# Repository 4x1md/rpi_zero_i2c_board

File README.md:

# I2C Peripherals Board for Raspberry Pi Zero

The board was developed for communicating some I2C peripherals connected to a Raspberry Pi Zero.

## Schematics

## 3D Model

## Questions? Suggestions?

You are more than welcome to contact me with any questions, suggestions or propositions regarding this project. Please drop an email to ```iosaaris =at= gmail dot com```.

## How to Support or Say Thanks

If you like this project, or found here some useful information and want to say thanks, or encourage me to do more, you can buy me a coffee!

---

73 de 4X1MD

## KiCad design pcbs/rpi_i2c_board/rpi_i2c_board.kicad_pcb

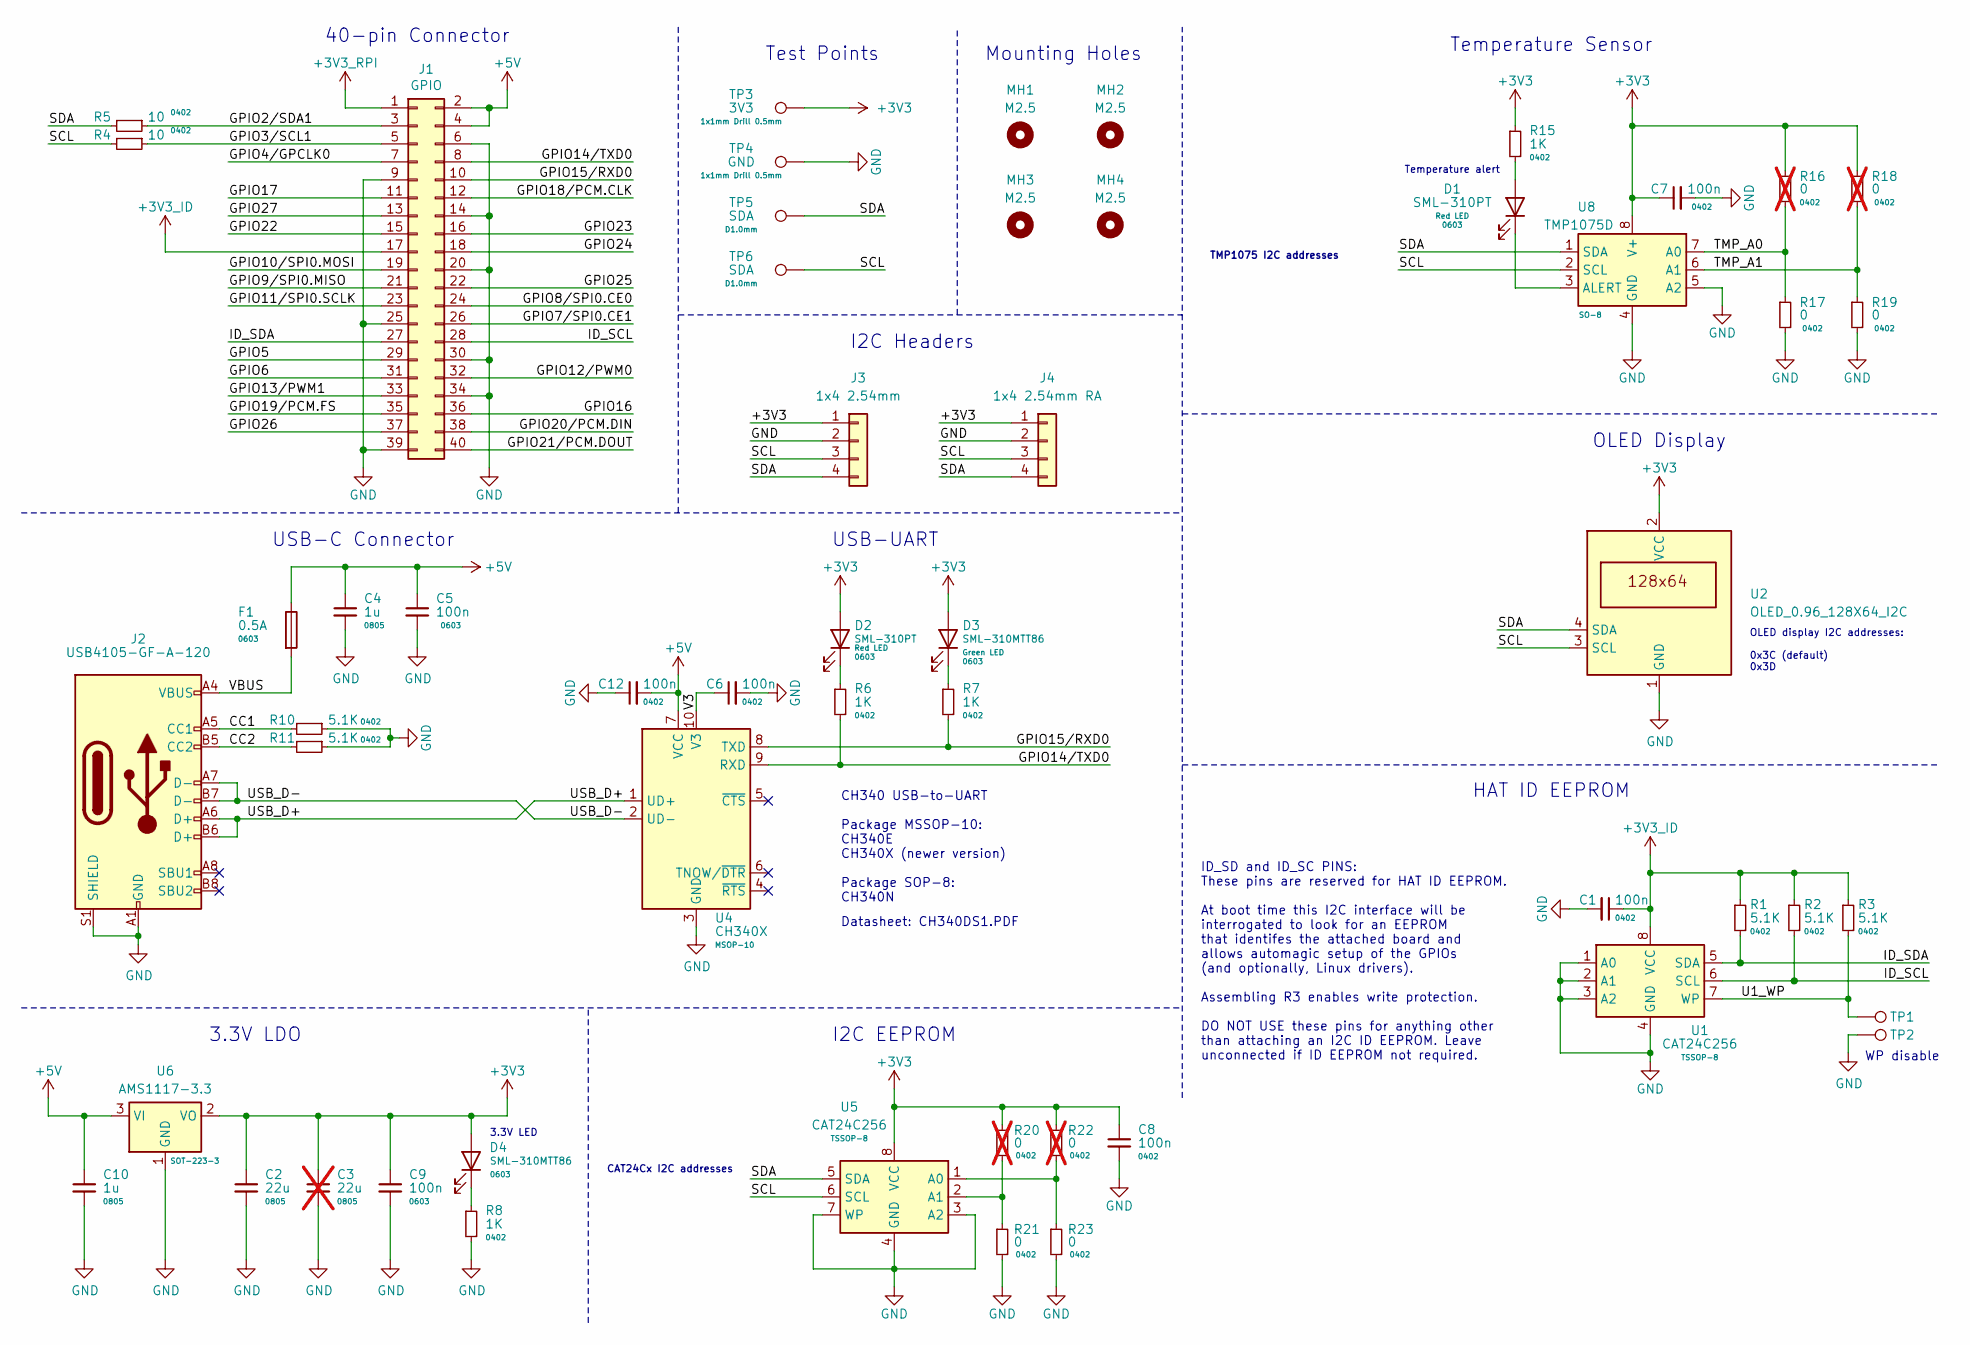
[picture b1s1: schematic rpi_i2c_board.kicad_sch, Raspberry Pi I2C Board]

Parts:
C1, C6, C7, C8, C12: 100n; C_0402_1005Metric
C2: 22u; C_0805_2012Metric
C3: 22u; C_0805_2012Metric; not fitted
C4, C10: 1u; C_0805_2012Metric
C5, C9: 100n; C_0603_1608Metric
D1, D2: SML-310PT; LED_0603_1608Metric
D3, D4: SML-310MTT86; LED_0603_1608Metric
F1: 0.5A; Fuse_0603_1608Metric
J1: GPIO; PinSocket_2x20_P2.54mm_Vertical
J2: USB4105-GF-A-120; USB_C_Receptacle_GCT_USB4105-xx-A_16P_TopMnt_Horizontal
J3: 1x4 2.54mm; PinSocket_1x04_P2.54mm_Vertical
J4: 1x4 2.54mm RA; PinHeader_1x04_P2.54mm_Horizontal
MH1, MH2, MH3, MH4: M2.5; MountingHole_2.7mm_M2.5_SolderMaskOpening
R1, R2, R3, R10, R11: 5.1K; R_0402_1005Metric
R4, R5: 10; R_0402_1005Metric
R6, R7, R8, R15: 1K; R_0402_1005Metric
R16, R18, R20, R22: 0; R_0402_1005Metric; not fitted
R17, R19, R21, R23: 0; R_0402_1005Metric
TP1: ID SDA; TestPoint_THTPad_1.0x1.0mm_Drill0.5mm
TP2: ID SCL; TestPoint_THTPad_1.0x1.0mm_Drill0.5mm
TP3: 3V3; TestPoint_THTPad_1.0x1.0mm_Drill0.5mm
TP4: GND; TestPoint_THTPad_1.0x1.0mm_Drill0.5mm
TP5, TP6: SDA; TestPoint_Pad_D1.0mm
U1, U5: CAT24C256; TSSOP-8_4.4x3mm_P0.65mm
U2: OLED_0.96_128X64_I2C; OLED_0.96_128X64_I2C_2MH
U4: CH340X; MSOP-10_3x3mm_P0.5mm
U6: AMS1117-3.3; SOT-223-3_TabPin2
U8: TMP1075D; SO-8_3.9x4.9mm_P1.27mm

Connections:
+3V3: C2.1, C3.1, C7.1, C8.1, C9.1, D2.2 (A), D3.2 (A), D4.2 (A), J3.1, J4.1, R15.1, R16.1, R18.1, R20.1, R22.1, TP3.1, U2.2 (VCC), U5.8 (VCC), U6.2 (VO), U8.8 (V+)
+3V3_ID: C1.1, J1.17, R1.1, R2.1, R3.1, U1.8 (VCC)
+3V3_RPI: J1.1
+5V: C4.1, C5.1, C10.1, C12.2, F1.1, J1.2, J1.4, U4.7 (VCC), U6.3 (VI)
/CC1: J2.A5 (CC1), R10.2
/CC2: J2.B5 (CC2), R11.2
/GPIO2/SDA1: J1.3, R5.1
/GPIO3/SCL1: J1.5, R4.1
/GPIO4/GPCLK0: J1.7
/GPIO5: J1.29
/GPIO6: J1.31
/GPIO7/SPI0.CE1: J1.26
/GPIO8/SPI0.CE0: J1.24
/GPIO9/SPI0.MISO: J1.21
/GPIO10/SPI0.MOSI: J1.19
/GPIO11/SPI0.SCLK: J1.23
/GPIO12/PWM0: J1.32
/GPIO13/PWM1: J1.33
/GPIO14/TXD0: J1.8, R6.2, U4.9 (RXD)
/GPIO15/RXD0: J1.10, R7.2, U4.8 (TXD)
/GPIO16: J1.36
/GPIO17: J1.11
/GPIO18/PCM.CLK: J1.12
/GPIO19/PCM.FS: J1.35
/GPIO20/PCM.DIN: J1.38
/GPIO21/PCM.DOUT: J1.40
/GPIO22: J1.15
/GPIO23: J1.16
/GPIO24: J1.18
/GPIO25: J1.22
/GPIO26: J1.37
/GPIO27: J1.13
/ID_SCL: J1.28, R2.2, U1.6 (SCL)
/ID_SDA: J1.27, R1.2, U1.5 (SDA)
/SCL: J3.3, J4.3, R4.2, TP6.1, U2.3 (SCL), U5.6 (SCL), U8.2 (SCL)
/SDA: J3.4, J4.4, R5.2, TP5.1, U2.4 (SDA), U5.5 (SDA), U8.1 (SDA)
/TMP_A0: R16.2, R17.1, U8.7 (A0)
/TMP_A1: R18.2, R19.1, U8.6 (A1)
/U1_WP: R3.2, TP1.1, U1.7 (WP)
/USB_D+: J2.A6 (D+), J2.B6 (D+), U4.1 (UD+)
/USB_D-: J2.A7 (D-), J2.B7 (D-), U4.2 (UD-)
/V3: C6.1, U4.10 (V3)
/VBUS: F1.2, J2.A4 (VBUS), J2.A9 (VBUS), J2.B4 (VBUS), J2.B9 (VBUS)
GND: C1.2, C2.2, C3.2, C4.2, C5.2, C6.2, C7.2, C8.2, C9.2, C10.2, C12.1, J1.6, J1.9, J1.14, J1.20, J1.25, J1.30, J1.34, J1.39, J2.A1 (GND), J2.A12 (GND), J2.B1 (GND), J2.B12 (GND), J2.S1 (SHIELD), J3.2, J4.2, R8.2, R10.1, R11.1, R17.2, R19.2, R21.2, R23.2, TP2.1, TP4.1, U1.1 (A0), U1.2 (A1), U1.3 (A2), U1.4 (GND), U2.1 (GND), U4.3 (GND), U5.3 (A2), U5.4 (GND), U5.7 (WP), U6.1 (GND), U8.4 (GND), U8.5 (A2)
unnamed: D1.2 (A), R15.2
unnamed: D1.1 (K), U8.3 (ALERT)
unnamed: D2.1 (K), R6.1
unnamed: D3.1 (K), R7.1
unnamed: D4.1 (K), R8.1
unnamed: R22.2, R23.1, U5.1 (A0)
unnamed: R20.2, R21.1, U5.2 (A1)

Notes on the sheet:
OLED Display
USB-C Connector
Mounting Holes
3.3V LED
Test Points
3.3V LDO
USB-UART
I2C EEPROM
WP disable
ID_SD and ID_SC PINS: These pins are reserved for HAT ID EEPROM. At boot time this I2C interface will be interrogated to look for an EEPROM that identifes the attached board and allows automagic setup of the GPIOs (and optionally, Linux drivers). Assembling R3 enables write protection. DO NOT USE t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
CH340 USB-to-UART Package MSSOP-10: CH340E CH340X (newer version) Package SOP-8: CH340N
Datasheet: CH340DS1.PDF
40-pin Connector
OLED display I2C addresses: 0x3C (default) 0x3D
TMP1075 I2C addresses
CAT24Cx I2C addresses
Temperature Sensor
HAT ID EEPROM
Temperature alert
I2C Headers

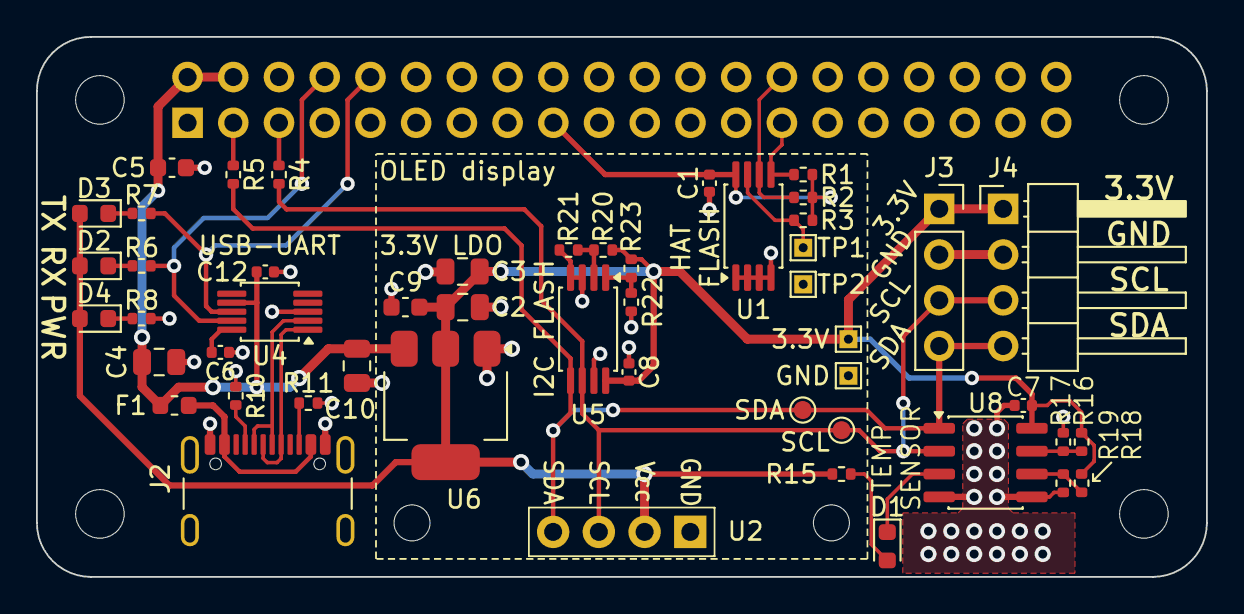
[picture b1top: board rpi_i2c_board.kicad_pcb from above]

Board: 2 copper layers, 65.0 x 30.0 mm, 55 parts (1 on the bottom side), 28 nets.

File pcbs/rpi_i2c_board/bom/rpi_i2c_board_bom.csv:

"Reference","Value","Footprint","Qty","FP","LSCS #"
"C1,C6,C7,C8,C12","100n","Capacitor_SMD:C_0402_1005Metric","5","0402","C1525"
"C2,C3","22u","Capacitor_SMD:C_0805_2012Metric","2","0805","C45783"
"C4,C10","1u","Capacitor_SMD:C_0805_2012Metric","2","0805","C28323"
"C5,C9","100n","Capacitor_SMD:C_0603_1608Metric","2","0603","C14663"
"D1,D2","SML-310PT","LED_SMD:LED_0603_1608Metric","2","0603","C123009"
"D3,D4","SML-310MTT86","LED_SMD:LED_0603_1608Metric","2","0603","C122984"
"F1","0.5A","Fuse:Fuse_0603_1608Metric","1","0603","C7472539"
"J2","USB4105-GF-A-120","Connector_USB:USB_C_Receptacle_GCT_USB4105-xx-A_16P_TopMnt_Horizontal","1","","C5184243"
"R1,R2,R3,R10,R11","5.1K","Resistor_SMD:R_0402_1005Metric","5","0402","C25905"
"R4,R5","10","Resistor_SMD:R_0402_1005Metric","2","0402","C25077"
"R6,R7,R8,R15","1K","Resistor_SMD:R_0402_1005Metric","4","0402","C11702"
"R16,R17,R18,R19,R20,R21,R22,R23","0","Resistor_SMD:R_0402_1005Metric","8","0402","C17168"
"U1,U5","CAT24C256","Package_SO:TSSOP-8_4.4x3mm_P0.65mm","2","TSSOP-8","C146734"
"U4","CH340X","Package_SO:MSOP-10_3x3mm_P0.5mm","1","MSOP-10","C3035748"
"U6","AMS1117-3.3","Package_TO_SOT_SMD:SOT-223-3_TabPin2","1","SOT-223-3","C6186"
"U8","TMP1075D","Package_SO:SO-8_3.9x4.9mm_P1.27mm","1","SO-8","C2878381"

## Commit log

2025-12-29 Create LICENSE.txt
    License for HW.
2025-12-29 Project schematics
2026-01-03 KiCAD project and PCB order files.
